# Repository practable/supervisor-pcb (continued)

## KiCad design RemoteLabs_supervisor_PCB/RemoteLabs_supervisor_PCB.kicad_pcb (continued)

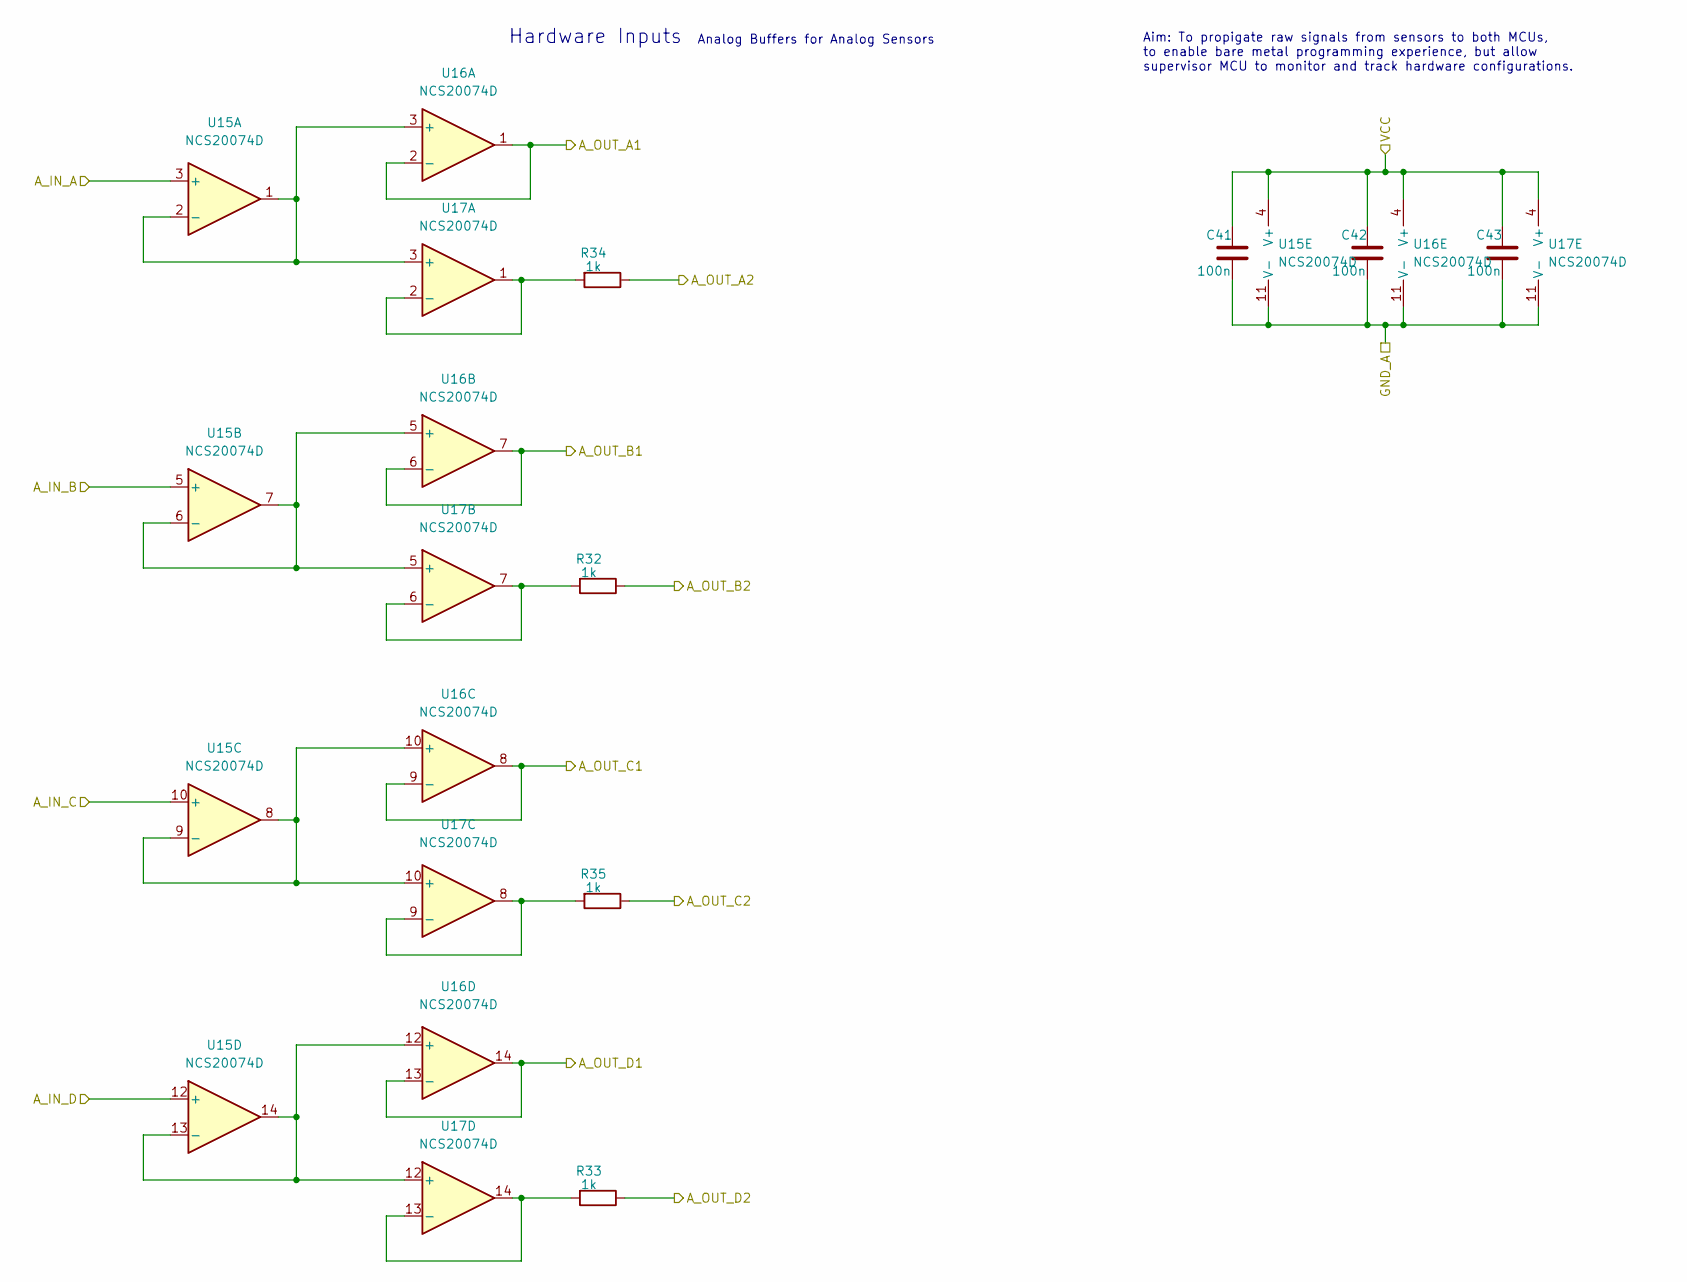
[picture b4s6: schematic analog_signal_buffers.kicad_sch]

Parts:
C41, C42, C43: 100n; C_0805_2012Metric_Pad1.18x1.45mm_HandSolder
R32, R33, R34, R35: 1k; R_0805_2012Metric_Pad1.20x1.40mm_HandSolder
U15, U16, U17: NCS20074D; SOIC-14_3.9x8.7mm_P1.27mm

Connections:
3V3_DC_MCU: C41.1, C42.1, C43.1, U15.4 (V+), U16.4 (V+), U17.4 (V+); also elsewhere on the board
/Analog Sensor Buffers/A_IN_C: U15.10 (+); also elsewhere on the board
/Analog Sensor Buffers/A_OUT_A1: U16.1, U16.2 (-); also elsewhere on the board
/Analog Sensor Buffers/A_OUT_A2: R34.1; also elsewhere on the board
/Analog Sensor Buffers/A_OUT_B1: U16.6 (-), U16.7; also elsewhere on the board
/Analog Sensor Buffers/A_OUT_B2: R32.1; also elsewhere on the board
/Analog Sensor Buffers/A_OUT_C1: U16.8, U16.9 (-); also elsewhere on the board
/Analog Sensor Buffers/A_OUT_C2: R35.1; also elsewhere on the board
/Analog Sensor Buffers/DB1: U15.1, U15.2 (-), U16.3 (+), U17.3 (+)
/Analog Sensor Buffers/DB1B: R34.2, U17.1, U17.2 (-)
/Analog Sensor Buffers/DB2: U15.6 (-), U15.7, U16.5 (+), U17.5 (+)
/Analog Sensor Buffers/DB2B: R32.2, U17.6 (-), U17.7
/Analog Sensor Buffers/DB3: U15.8, U15.9 (-), U16.10 (+), U17.10 (+)
/Analog Sensor Buffers/DB3B: R35.2, U17.8, U17.9 (-)
/Analog Sensor Buffers/DB4: U15.13 (-), U15.14, U16.12 (+), U17.12 (+)
/Analog Sensor Buffers/DB4B: R33.2, U17.13 (-), U17.14
A_BUFFER_IN: U15.12 (+); also elsewhere on the board
A_BUFFER_OUT_A: U16.13 (-), U16.14; also elsewhere on the board
A_BUFFER_OUT_B: R33.1; also elsewhere on the board
M_I_SENSE_1: U15.3 (+); also elsewhere on the board
M_I_SENSE_2: U15.5 (+); also elsewhere on the board

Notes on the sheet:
Hardware Inputs
Analog Buffers for Analog Sensors
Aim: To propigate raw signals from sensors to both MCUs, to enable bare metal programming experience, but allow supervisor MCU to monitor and track hardware configurations.

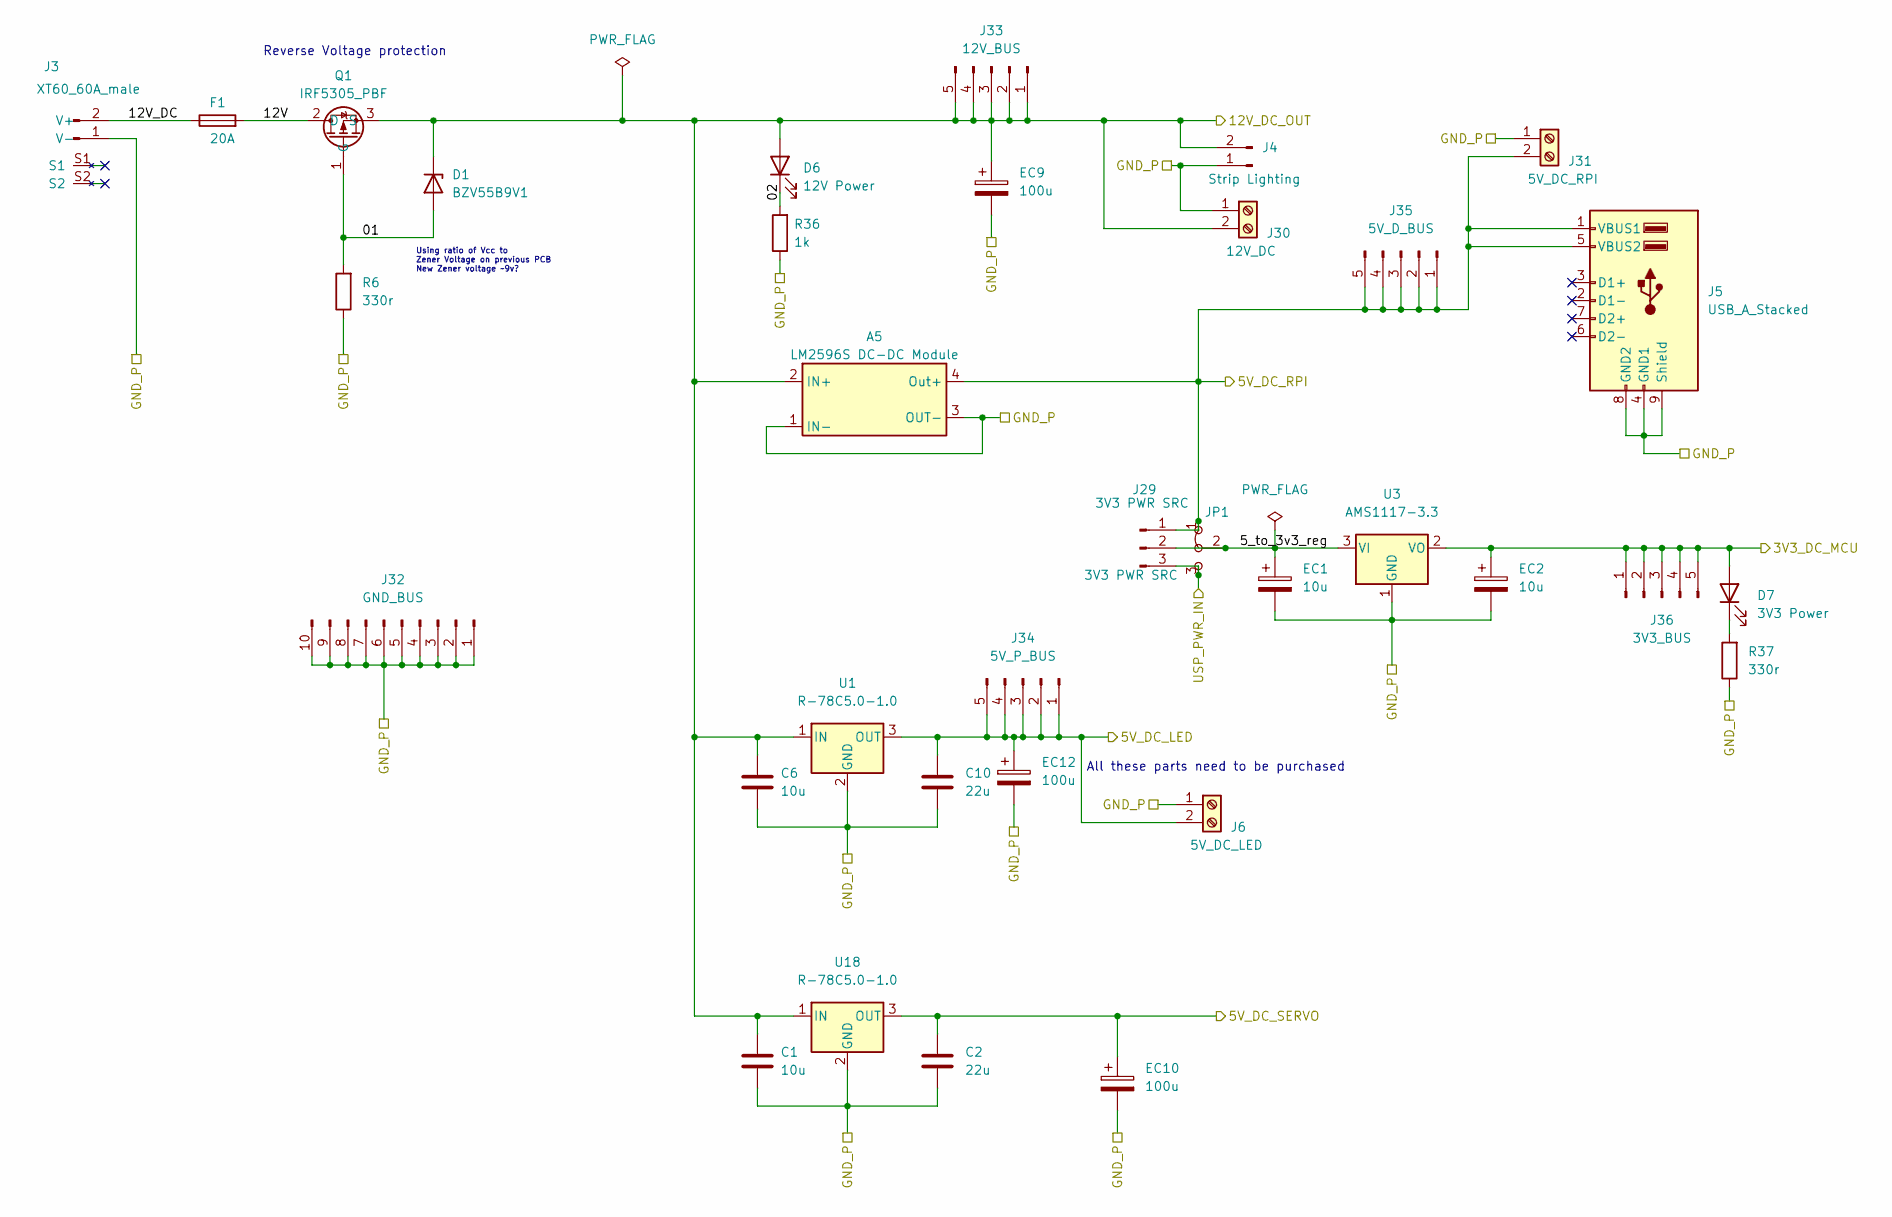
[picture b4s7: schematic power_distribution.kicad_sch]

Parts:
A5: LM2596S DC-DC Module
C1, C6: 10u; C_0805_2012Metric_Pad1.18x1.45mm_HandSolder
C2, C10: 22u; C_0805_2012Metric_Pad1.18x1.45mm_HandSolder
D1: BZV55B9V1; D_MiniMELF
D6: 12V Power; D_0805_2012Metric_Pad1.15x1.40mm_HandSolder
D7: 3V3 Power; D_0805_2012Metric_Pad1.15x1.40mm_HandSolder
EC1, EC2: 10u; CP_Elec_4x5.4
EC9, EC10, EC12: 100u; CP_Elec_6.3x7.7
F1: 20A; Fuseholder_Cylinder-5x20mm_Stelvio-Kontek_PTF78_Horizontal_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
J3: XT60_60A_male; AMASS_XT60PW-M
J4: Strip Lighting; Molex_KK-254_AE-6410-02A_1x02_P2.54mm_Vertical
J5: USB_A_Stacked; USB_A_Wuerth_61400826021_Horizontal_Stacked
J6: 5V_DC_LED; TerminalBlock_Altech_AK300-2_P5.00mm
J29: 3V3 PWR SRC; PinHeader_1x03_P2.54mm_Vertical
J30: 12V_DC; TerminalBlock_Altech_AK300-2_P5.00mm
J31: 5V_DC_RPI; TerminalBlock_Altech_AK300-2_P5.00mm
J32: GND_BUS; PinHeader_1x10_P1.27mm_Vertical
J33: 12V_BUS; PinHeader_1x05_P2.54mm_Vertical
J34: 5V_P_BUS; PinHeader_1x05_P2.54mm_Vertical
J35: 5V_D_BUS; PinHeader_1x05_P2.54mm_Vertical
J36: 3V3_BUS; PinHeader_1x05_P2.54mm_Vertical
JP1: 3V3 PWR SRC; SolderJumper-3_P1.3mm_Bridged12_RoundedPad1.0x1.5mm
Q1: IRF5305_PBF; TO-220-3_Vertical
R6, R37: 330r; R_0805_2012Metric_Pad1.20x1.40mm_HandSolder
R36: 1k; R_0805_2012Metric_Pad1.20x1.40mm_HandSolder
U1, U18: R-78C5.0-1.0; Converter_DCDC_RECOM_R-78E-0.5_THT
U3: AMS1117-3.3; SOT-223-3_TabPin2

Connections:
3V3_DC_MCU: D7.2 (A), EC2.1, J36.1, J36.2, J36.3, J36.4, J36.5, U3.2 (VO); also elsewhere on the board
5V_DC_LED: C10.1, EC12.1, J6.2, J34.1, J34.2, J34.3, J34.4, J34.5, U1.3 (OUT); also elsewhere on the board
5V_DC_RPI: A5.4 (Out+), J5.1 (VBUS1), J5.5 (VBUS2), J29.1, J31.2, J35.1, J35.2, J35.3, J35.4, J35.5, JP1.1 (A); also elsewhere on the board
5V_DC_SERVO: C2.1, EC10.1, U18.3 (OUT); also elsewhere on the board
12V_DC_BUS: A5.2 (IN+), C1.1, C6.1, D1.1 (K), D6.2 (A), EC9.1, J4.2, J30.2, J33.1, J33.2, J33.3, J33.4, J33.5, Q1.3 (S), U1.1 (IN), U18.1 (IN); also elsewhere on the board
/Power Input & Distribution/01: D1.2 (A), Q1.1 (G), R6.2
/Power Input & Distribution/02: D6.1 (K), R36.2
/Power Input & Distribution/5_to_3v3_reg: EC1.1, J29.2, JP1.2 (C), U3.3 (VI)
/Power Input & Distribution/12V: F1.2, Q1.2 (D)
/Power Input & Distribution/12V_DC: F1.1, J3.2 (V+)
unnamed: D7.1 (K), R37.2
USB_BUS: J29.3, JP1.3 (B); also elsewhere on the board

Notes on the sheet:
Reverse Voltage protection
Using ratio of Vcc to Zener Voltage on previous PCB New Zener voltage ~9v?
All these parts need to be purchased

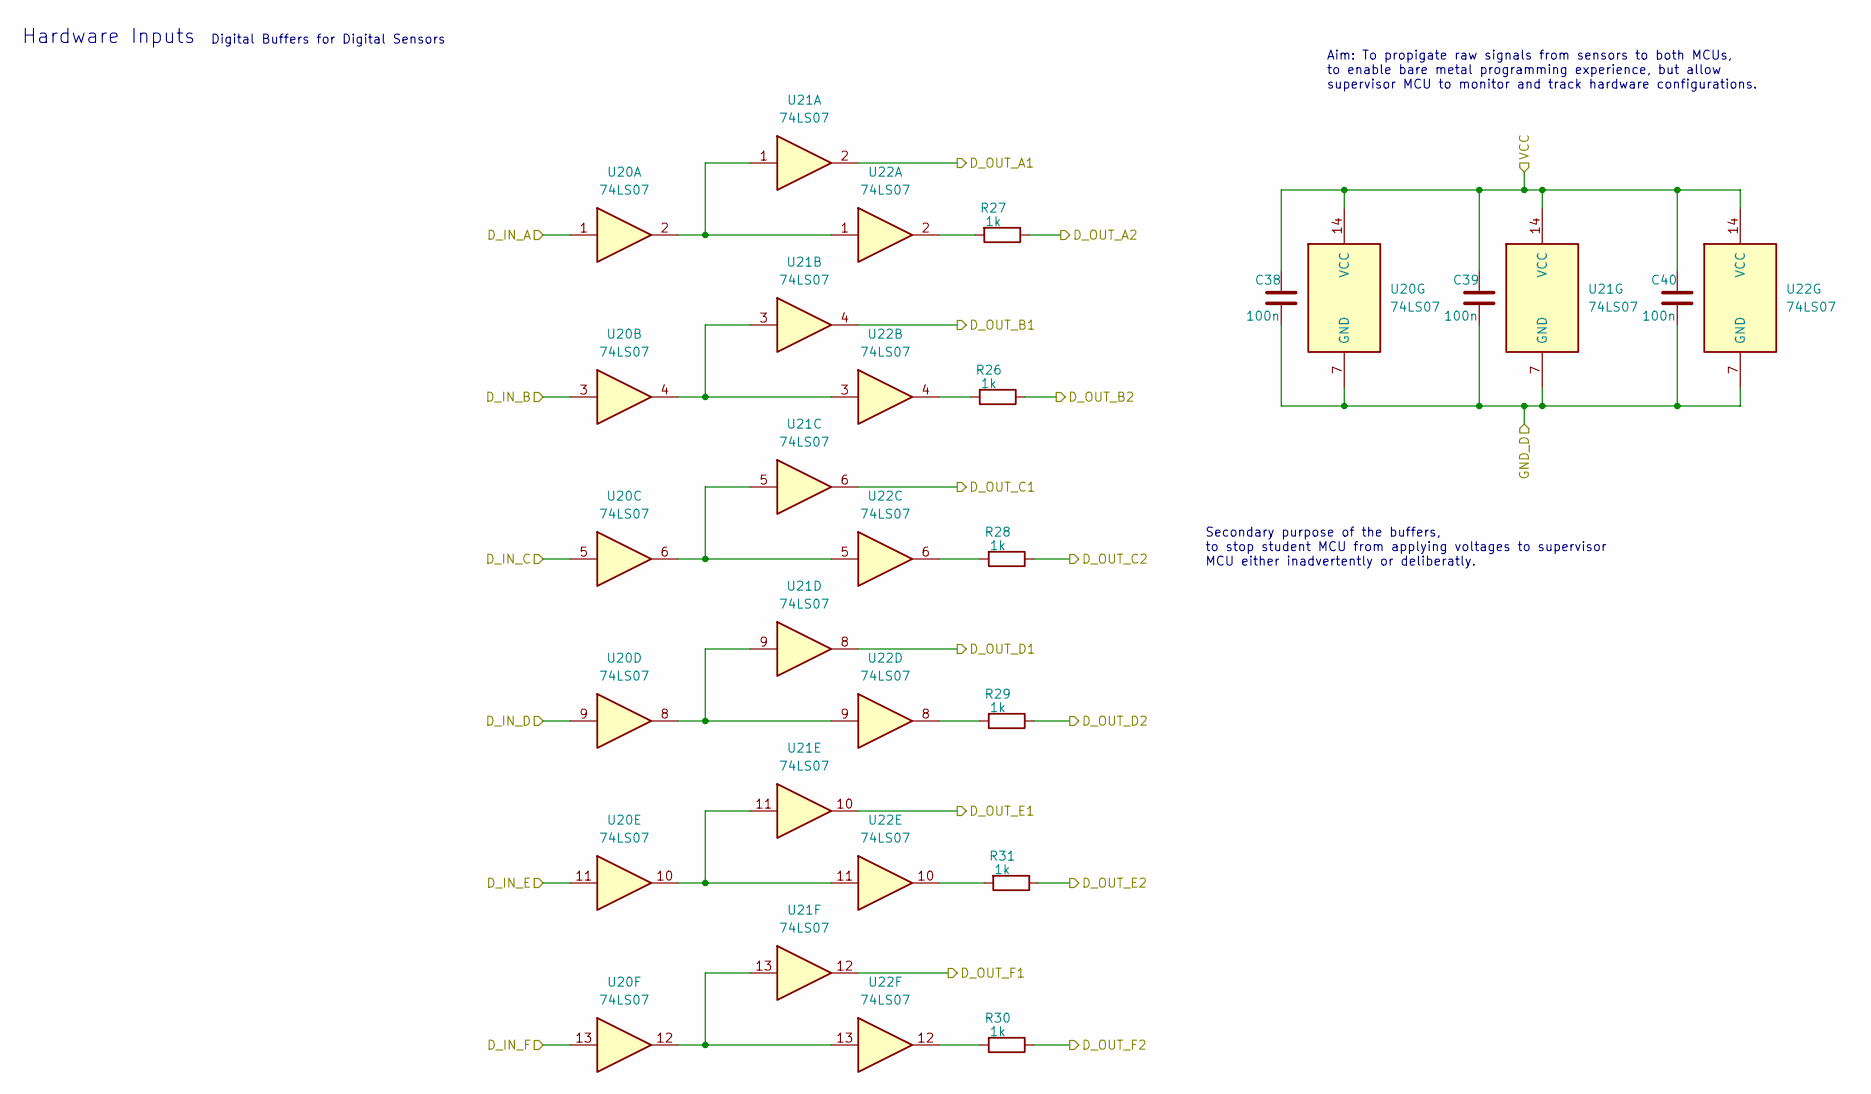
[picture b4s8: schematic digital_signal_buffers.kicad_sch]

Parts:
C38, C39, C40: 100n; C_0805_2012Metric_Pad1.18x1.45mm_HandSolder
R26, R27, R28, R29, R30, R31: 1k; R_0805_2012Metric_Pad1.20x1.40mm_HandSolder
U20, U21, U22: 74LS07; SOIC-14_3.9x8.7mm_P1.27mm

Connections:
3V3_DC_MCU: C38.1, C39.1, C40.1, U20.14 (VCC), U21.14 (VCC), U22.14 (VCC); also elsewhere on the board
/Digital Sensor Buffers/D_IN_A: U20.1; also elsewhere on the board
/Digital Sensor Buffers/D_IN_B: U20.3; also elsewhere on the board
/Digital Sensor Buffers/D_IN_C: U20.5; also elsewhere on the board
/Digital Sensor Buffers/D_IN_D: U20.9; also elsewhere on the board
/Digital Sensor Buffers/D_IN_E: U20.11; also elsewhere on the board
/Digital Sensor Buffers/D_OUT_A1: U21.2; also elsewhere on the board
/Digital Sensor Buffers/D_OUT_B1: U21.4; also elsewhere on the board
/Digital Sensor Buffers/D_OUT_C1: U21.6; also elsewhere on the board
/Digital Sensor Buffers/D_OUT_D1: U21.8; also elsewhere on the board
/Digital Sensor Buffers/D_OUT_E1: U21.10; also elsewhere on the board
/Digital Sensor Buffers/D_OUT_F1: U21.12; also elsewhere on the board
LIMIT_1: R27.1; also elsewhere on the board
LIMIT_2: R26.1; also elsewhere on the board
unnamed: R26.2, U22.4
unnamed: R27.2, U22.2
unnamed: R28.2, U22.6
unnamed: R29.2, U22.8
unnamed: R30.2, U22.12
unnamed: R31.2, U22.10
unnamed: U20.2, U21.1, U22.1
unnamed: U20.4, U21.3, U22.3
unnamed: U20.6, U21.5, U22.5
unnamed: U20.8, U21.9, U22.9
unnamed: U20.10, U21.11, U22.11
unnamed: U20.12, U21.13, U22.13
OE_A: R28.1; also elsewhere on the board
OE_B: R31.1; also elsewhere on the board
OE_IDX: R29.1; also elsewhere on the board
STPPR_FAULT: U20.13; also elsewhere on the board
STU_STP_FLT: R30.1; also elsewhere on the board

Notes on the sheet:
Hardware Inputs
Digital Buffers for Digital Sensors
Secondary purpose of the buffers, to stop student MCU from applying voltages to supervisor MCU either inadvertently or deliberatly.
Aim: To propigate raw signals from sensors to both MCUs, to enable bare metal programming experience, but allow supervisor MCU to monitor and track hardware configurations.

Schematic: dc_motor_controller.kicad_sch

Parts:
A3: Infineon Motor Shield Uno; Infineon Motor Sheild hiddenPins
F2: 2A; Fuseholder_Cylinder-5x20mm_Stelvio-Kontek_PTF78_Horizontal_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
J16: DC Motor PWR; TerminalBlock_Altech_AK300-2_P5.00mm
J17: MotorController Output; TerminalBlock_Altech_AK300-3_P5.00mm
J18: DC Motor Output; TerminalBlock_Altech_AK300-3_P5.00mm
R12, R13: 470r; R_0805_2012Metric_Pad1.20x1.40mm_HandSolder

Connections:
5V_DC_SERVO: A3.5 (5V); also elsewhere on the board
12V_DC_BUS: F2.1; also elsewhere on the board
/DC Motor Controller/ENABLE: A3.27 (INH_1), A3.28 (INH_2); also elsewhere on the board
/DC Motor Controller/HC: F2.2, J16.1
/DC Motor Controller/HC1: J17.3, J18.1
/DC Motor Controller/HC2: J17.2, J18.2
/DC Motor Controller/HC3: J17.1, J18.3
/DC Motor Controller/IN_1: A3.18 (IN_1); also elsewhere on the board
/DC Motor Controller/IN_2: A3.26 (IN_2); also elsewhere on the board
/DC Motor Controller/PENDULUM_PIN_1: A3.19 (D4); also elsewhere on the board
M_I_SENSE_1: A3.9 (IS_1), R12.2; also elsewhere on the board
M_I_SENSE_2: A3.10 (IS_2), R13.2; also elsewhere on the board
PEND_ENABLE: A3.20 (D5); also elsewhere on the board
SERVO_1: A3.24 (D9); also elsewhere on the board
STUDNT_LED1: A3.21 (D6); also elsewhere on the board
STUDNT_LED2: A3.22 (D7); also elsewhere on the board
STUDNT_LED3: A3.23 (D8); also elsewhere on the board
SUP_LED1: A3.25 (D10); also elsewhere on the board
SUP_LED2: A3.17 (D2); also elsewhere on the board

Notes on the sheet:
If the high side drain current is zero (ISD(HS) = 0A) the offset current IIS = IIS(offset) still will be driven. The external resistor RIS determines the voltage per IS output current. The voltage can be calculated by VIS = RIS . IIS. In case of a fault condition the status output is connected to a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
Current sense outputs: I(load) = dk(ilis)*(I(is)-I(is_offset)) Differential Current Sense ratio dk(ilis): dk(ilis) = (I(L2)-I(L1))/((I(is))*(I(L2))-(I(is)*(I(L1)))
Assume 6.5mA MAX V = 6.5 * 500 / 1000 V = 3.25v
These Pins are connected OFF BOARD with wire
Pendulum Notes: Pinout: Enable Drive Pin 1 Load pin 2 STUDENT_ENABLE pin 3 Stu LED 1 pin 4 Stu LED 2 pin 5 Stu LED 3 pin 6 Sup LED 3 pin 7 Sup LED 1 pin 8 Sup LED 2 Pin 2 is enable, when supervisor enables student control HIGH is received here additionally to differentiate control of LEDs
Must be 1% tolerance for 3.3v max
INH is active low, so renamed as ENABLE (Active HIGH to enable)
I(is_lim) @ Vs = 12v & Tj = 100degC = 5.25 mA
INH Pins can be joined
None of these pins are connected on Infineon Board, so can be used for pendulum driver

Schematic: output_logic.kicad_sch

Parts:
C24, C25, C26, C27, C28, C29, C30: 100n; C_0805_2012Metric_Pad1.18x1.45mm_HandSolder
U8: 4069; SOIC-14_3.9x8.7mm_P1.27mm
U9, U10, U11, U12: 4081; SOIC-14_3.9x8.7mm_P1.27mm
U13, U14: 74HC86; SOIC-14_3.9x8.7mm_P1.27mm

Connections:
3V3_DC_MCU: C24.1, C25.1, C26.1, C27.1, C28.1, C29.1, C30.1, U8.14 (VDD), U9.14 (VDD), U10.14 (VDD), U11.14 (VDD), U12.14 (VDD), U13.14 (VCC), U14.14 (VCC); also elsewhere on the board
/DC Motor Controller/ENABLE: U14.6; also elsewhere on the board
/DC Motor Controller/IN_1: U9.3; also elsewhere on the board
/DC Motor Controller/IN_2: U9.10; also elsewhere on the board
/DC Motor Controller/PENDULUM_PIN_1: U13.6; also elsewhere on the board
/Output Logic/DIRECTION_OUT: U13.3; also elsewhere on the board
/Output Logic/MCU_PIXEL_SELECT: U8.5, U12.9; also elsewhere on the board
/Output Logic/MCU_STEP_SELECT: U8.3, U10.2, U10.6, U10.9, U10.13; also elsewhere on the board
/Output Logic/PIXEL_DATA_OUT: U14.8; also elsewhere on the board
/Output Logic/STEP_RST_OUT: U13.11; also elsewhere on the board
/Output Logic/STEP_SLP_OUT: U13.8; also elsewhere on the board
/Output Logic/STUDENT_DIRECTION: U10.1; also elsewhere on the board
/Output Logic/STUDENT_MOTOR_EN: U12.5; also elsewhere on the board
/Output Logic/STUDENT_MOTOR_PWM: U12.1; also elsewhere on the board
/Output Logic/STUDENT_PIXEL_DATA: U12.8; also elsewhere on the board
/Output Logic/STUDENT_STEP: U10.5; also elsewhere on the board
/Output Logic/STUDENT_STEP_RST: U10.12; also elsewhere on the board
/Output Logic/STUDENT_STEP_SLP: U10.8; also elsewhere on the board
/Output Logic/SUPERVISOR_DIRECTION: U11.1; also elsewhere on the board
/Output Logic/SUPERVISOR_MOTOR_EN: U9.12; also elsewhere on the board
/Output Logic/SUPERVISOR_MOTOR_PWM: U9.5; also elsewhere on the board
/Output Logic/SUPERVISOR_PIXEL_DATA: U12.12; also elsewhere on the board
/Output Logic/SUPERVISOR_STEP: U11.5; also elsewhere on the board
/Output Logic/SUPERVISOR_STEP_RST: U11.12; also elsewhere on the board
/Output Logic/SUPERVISOR_STEP_SLP: U11.8; also elsewhere on the board
unnamed: U8.2, U9.6, U9.13
unnamed: U10.3, U13.1
unnamed: U10.4, U13.4
unnamed: U10.10, U13.9
unnamed: U10.11, U13.12
unnamed: U11.3, U13.2
unnamed: U11.4, U13.5
unnamed: U11.10, U13.10
unnamed: U11.11, U13.13
unnamed: U8.4, U11.2, U11.6, U11.9, U11.13
unnamed: U12.3, U14.1
unnamed: U12.4, U14.4
unnamed: U12.10, U14.9
unnamed: U12.11, U14.10
unnamed: U8.6, U12.13
unnamed: U9.4, U14.2
unnamed: U9.1, U9.8, U14.3
unnamed: U9.11, U14.5
PEND_ENABLE: U8.1, U12.2, U12.6; also elsewhere on the board
SUP_LED1: U9.2; also elsewhere on the board
SUP_LED2: U9.9; also elsewhere on the board

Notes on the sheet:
Pixel Output
Hardware Outputs
Decoupling Caps
Stepper Motor Outputs
Aim: To give supervisor MCU ability to block control of experimental hardware by the student MCU, and allow supervisor MCU master control of all experimental hardware.
DC Motor Outputs
Spare Gates
PWM is assigned to either Motor driver board IN_1 or IN_2 based on 2 direction pins sent by Supervisor MCU. This would allow supervisor to drive both pins high, leading to SHOOT THROUGH. Student has the same inputs to motor driver, but direction pins are spoofed through the supervisor, so superviso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
Supervisor also controls whether PWM control is enabled from student MCU

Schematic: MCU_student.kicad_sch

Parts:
A1: Arduino_Nano_33_IoT; Arduino_Nano
C2A1: 100p; C_0805_2012Metric_Pad1.18x1.45mm_HandSolder
C2B1, C4, C8, C9, C11, C12: 100n; C_0805_2012Metric_Pad1.18x1.45mm_HandSolder
C3: 4n7; C_0805_2012Metric_Pad1.18x1.45mm_HandSolder
C5: 10n; C_0805_2012Metric_Pad1.18x1.45mm_HandSolder
C7: 1u; CP_EIA-2012-12_Kemet-R_Pad1.30x1.05mm_HandSolder
C14, C15: 12p; C_0805_2012Metric_Pad1.18x1.45mm_HandSolder
D2: PMEG6020ER; Nexperia_CFP3_SOD-123W
D3: PRTR5V0U2X; SOT-143
D8: Yellow; D_0805_2012Metric_Pad1.15x1.40mm_HandSolder
EC3, EC4: 10u; CP_Elec_4x5.4
FB1: BLM18PG471; L_0805_2012Metric_Pad1.05x1.20mm_HandSolder
J7: USB_B_Mini; USB_Mini-B_Lumberg_2486_01_Horizontal
J8: MCU_Header; PinHeader_1x08_P2.54mm_Vertical
J9: Spare Student GPIOs; PinHeader_1x04_P2.54mm_Vertical
J10: ShiftReg_Header; PinHeader_1x08_P2.54mm_Vertical
J11: SPI Student; PinHeader_1x03_P2.54mm_Vertical
J28: student_PA03; PinHeader_1x01_P1.27mm_Vertical
JP3, JP4: Xtal/IC; SolderJumper-3_P1.3mm_Bridged12_RoundedPad1.0x1.5mm_NumberL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
JP10: Reset GND; SolderJumper-2_P1.3mm_Open_Pad1.0x1.5mm
R3: 2k2; R_0805_2012Metric_Pad1.20x1.40mm_HandSolder
R4, R38: 330r; R_0805_2012Metric_Pad1.20x1.40mm_HandSolder
R7: 1M; R_0805_2012Metric_Pad1.20x1.40mm_HandSolder
R40: 0r; R_0805_2012Metric_Pad1.20x1.40mm_HandSolder
SW2: Student Reset; SW_Push_1P1T_NO_CK_KSC6xxJ
U2: TCYSH14F; SOT-23-5_HandSoldering
U4: ATSAMD21G18A-M; QFN-48-1EP_7x7mm_P0.5mm_EP5.15x5.15mm
U5: 4094; SOIC-16_3.9x9.9mm_P1.27mm
X1: 32.768kHz; Oscillator_SMD_Abracon_ASE-4Pin_3.2x2.5mm

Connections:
3V3_DC_MCU: A1.17 (3V3), C2A1.1, C4.1, C8.1, C9.2, C12.1, EC3.1, FB1.1, JP4.1 (A), R3.2, U2.5 (VCC), U4.17 (VDDIO), U4.36 (VDDIO), U4.44 (VDDIN), U5.15 (OE), U5.16 (VCC); also elsewhere on the board
/Analog Sensor Buffers/A_OUT_A2: A1.26 (A7), U4.48 (PB03); also elsewhere on the board
/Analog Sensor Buffers/A_OUT_B2: A1.25 (A6), U4.14 (PA09); also elsewhere on the board
/Analog Sensor Buffers/A_OUT_C2: A1.22 (A3), U4.15 (PA10); also elsewhere on the board
/Output Logic/STUDENT_DIRECTION: J10.5, U5.14 (Q4); also elsewhere on the board
/Output Logic/STUDENT_MOTOR_EN: J10.1, U5.4 (Q0); also elsewhere on the board
/Output Logic/STUDENT_MOTOR_PWM: A1.13 (D10), U4.30 (PA21); also elsewhere on the board
/Output Logic/STUDENT_PIXEL_DATA: A1.8 (D5), U4.10 (PA05); also elsewhere on the board
/Output Logic/STUDENT_STEP: A1.9 (D6), U4.9 (PA04); also elsewhere on the board
/Output Logic/STUDENT_STEP_RST: J10.7, U5.12 (Q6); also elsewhere on the board
/Output Logic/STUDENT_STEP_SLP: J10.6, U5.13 (Q5); also elsewhere on the board
/Student MCU/DC_MOTOR_DIR1: A1.15 (D12), U4.28 (PA19); also elsewhere on the board
/Student MCU/DC_MOTOR_DIR2: A1.10 (D7), U4.11 (PA06); also elsewhere on the board
/Student MCU/HSE_IN: JP3.3 (B), U2.4, U4.1 (PA00)
/Student MCU/HSE_OUT: R40.2, U4.2 (PA01)
/Student MCU/LATCH: A1.11 (D8), J11.3, U4.27 (PA18), U5.1 (STROBE)
/Student MCU/MCU_RESET: A1.3 (~RESET), A1.28 (~RESET), R4.2, SW2.2; also elsewhere on the board
/Student MCU/MODE_2: J8.8, U4.23 (PA14)
/Student MCU/MOSI: A1.14 (D11), J11.1, U4.25 (PA16), U5.2 (DATA)
/Student MCU/PROG_RX: A1.2 (D0/RX), U4.38 (PB23); also elsewhere on the board
/Student MCU/PROG_TX: A1.1 (D1/TX), U4.37 (PB22); also elsewhere on the board
/Student MCU/SCK: A1.16 (D13), J11.2, R38.2, U4.26 (PA17), U5.3 (CLOCK)
/Student MCU/SERVO_1: A1.12 (D9), U4.29 (PA20); also elsewhere on the board
/Student MCU/SERVO_2: U4.21 (PA12); also elsewhere on the board
/Student MCU/SHIFT_1: J10.2, U5.5 (Q1)
/Student MCU/SHIFT_2: J10.3, U5.6 (Q2)
/Student MCU/SHIFT_3: J10.4, U5.7 (Q3)
/Student MCU/SHIFT_7: J10.8, U5.11 (Q7)
/Student MCU/SPARE_3: J9.4, U4.22 (PA13)
/Student MCU/USB_N: D3.3 (I/O2), J7.2 (D-), U4.33 (PA24)
/Student MCU/USB_P: D3.2 (I/O1), J7.3 (D+), U4.34 (PA25)
LIMIT_1: A1.23 (A4), U4.7 (PB08); also elsewhere on the board
LIMIT_2: U4.31 (PA22); also elsewhere on the board
unnamed: C2A1.2, C2B1.1, JP10.2 (B), R3.1, R4.1, U4.40 (~RESET)
unnamed: C3.1, D3.1 (GND), J7.6 (Shield), R7.2
unnamed: C5.1, JP3.1 (A), JP4.2 (C), X1.4 (Vdd)
unnamed: C7.1, U4.43 (VDDCORE)
unnamed: C11.2, EC4.1, FB1.2, U4.6 (VDDANA)
unnamed: C14.1, JP3.2 (C), X1.1 (TRI)
unnamed: C15.1, R40.1, U2.2, X1.3 (OUT)
unnamed: D2.2 (A), D3.4 (VCC), J7.1 (VBUS)
unnamed: D8.2 (A), R38.1
unnamed: J8.1, U4.13 (PA08)
unnamed: J8.2, U4.24 (PA15)
unnamed: J8.3, U4.32 (PA23)
unnamed: J8.4, U4.39 (PA27)
unnamed: J8.5, U4.41 (PA28)
unnamed: J8.6, U4.45 (PA30)
unnamed: J8.7, U4.46 (PA31)
unnamed: J28.1, U4.4 (PA03)
OE_A: A1.6 (D3), U4.20 (PB11); also elsewhere on the board
OE_B: A1.5 (D2), U4.19 (PB10); also elsewhere on the board
OE_IDX: A1.7 (D4), U4.12 (PA07); also elsewhere on the board
STUDNT_LED1: A1.21 (A2), J9.3, U4.16 (PA11); also elsewhere on the board
STUDNT_LED2: A1.20 (A1), J9.2, U4.47 (PB02); also elsewhere on the board
STUDNT_LED3: A1.19 (A0), J9.1, U4.3 (PA02); also elsewhere on the board
STU_STP_FLT: A1.24 (A5), U4.8 (PB09); also elsewhere on the board
USB_BUS: D2.1 (K); also elsewhere on the board

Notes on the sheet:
SAMD21 BareMetal MCU Slot
Shift Register to Expand Number of Output Pins
Functions Available on Raw MCU Removed for IoT Board to free pins
A4 & A5 Internal pull up for I2C Bus Avoid analogRead
PCB Laid out for Either: - Arduino Nano 33 IoT OR - SAMD21 MCU Only components for 1 of these options should be populated, the other left emtpty Connectors in the middle are shared by both options and should always be populated
Should be low ESR
For Osc IC - R? Unpopulated - C? & C? Unpopulated - C? ~ 10n - All Jumpers 2 - 1 For Xtal - R? = 0ohm to 47ohm - C? & C? Value = 2 *(Cxtal -Cstray) - All Jumpers 2 - 3 TCYSH14F - No Idea, probably omit for Xtal
Main Differences: No need for "Student Enable pins" as this is a supervisor only function No need for any pins that detect input from student No Mode Pins
Additional Ferrite Bead here?
C2A or C2B IF C2B -> R3 = 10k
External Clock Package IC
Student MCU
Arduino Nano IoT 33 Devboard Slot
SAMD21 BareMetal USB I/F
Replicates LED_BUILTIN on Arduino Pin: D13

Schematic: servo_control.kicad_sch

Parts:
J20: Servo_A; PinHeader_1x03_P2.54mm_Vertical
J21: Servo_B; PinHeader_1x03_P2.54mm_Vertical

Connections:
5V_DC_SERVO: J20.2, J21.2; also elsewhere on the board
SERVO_1: J20.1; also elsewhere on the board
SERVO_2: J21.1; also elsewhere on the board

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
